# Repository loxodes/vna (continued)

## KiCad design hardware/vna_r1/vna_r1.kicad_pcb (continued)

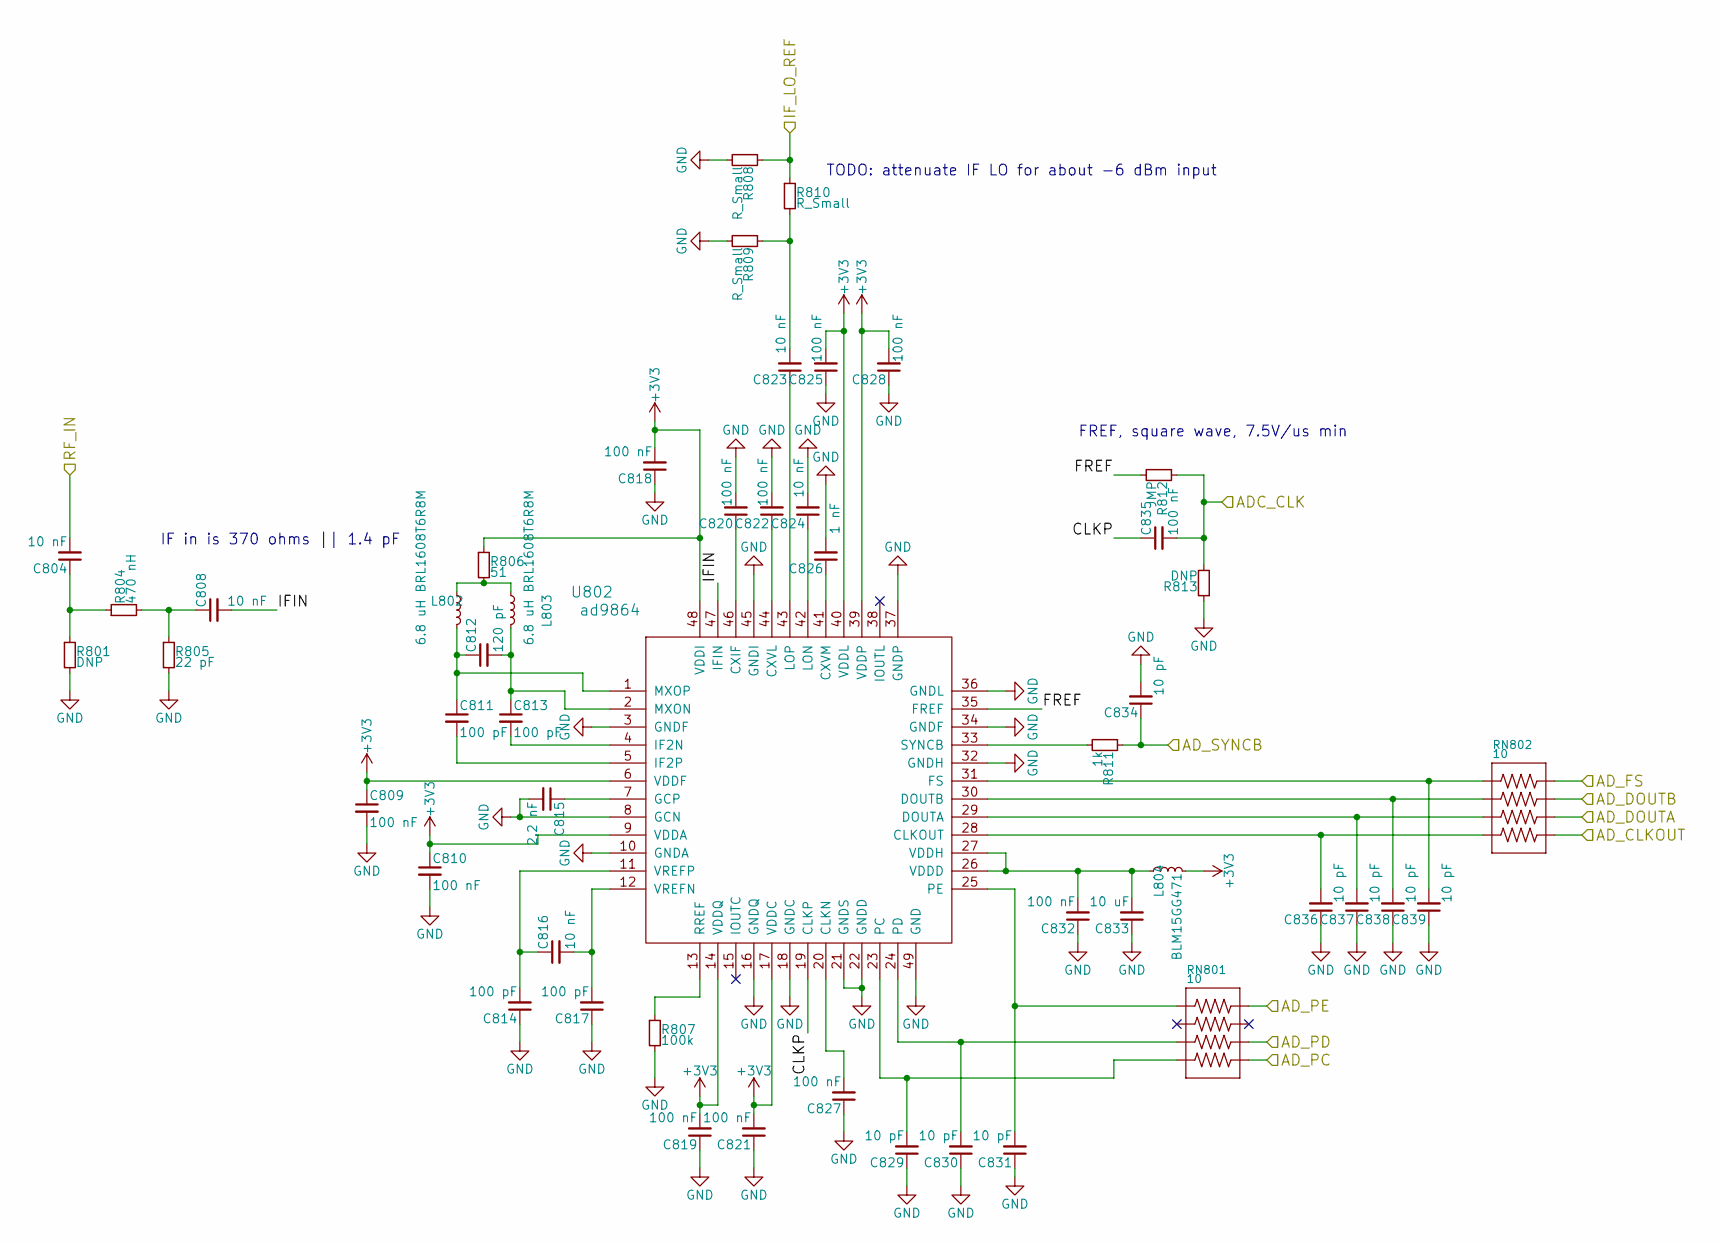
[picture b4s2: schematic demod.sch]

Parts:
C504, C508, C516, C523, C524: 10 nF; C_0402
C509, C510, C518, C519, C520, C521, C522, C525, C527, C528, C532, C535: 100 nF; C_0402
C511, C513, C514, C517: 100 pF; C_0402
C512: 120 pF; C_0402
C515: 2.2 nF; C_0402
C526: 1 nF; C_0402
C529, C530, C531, C534, C536, C537, C538, C539: 10 pF; C_0402
C533: 10 uF; C_0603
L502, L503: 6.8 uH BRL1608T6R8M; R_0603
L504: BLM15GG471; R_0402
R501, R513: DNP; R_0402
R504: 470 nH; R_0402
R505: 22 pF; R_0402
R506: 51; R_0402
R507: 100k; R_0402
R508, R509, R510: R_Small; R_0402
R511: 1k; R_0402
R512: JMP; R_0402
RN501, RN502: 10; RN0804
U502: ad9864; QFN-48-1EP_7x7mm_Pitch0.5mm

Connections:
+3V3: C509.1, C510.1, C518.2, C519.2, C521.2, C525.2, C528.2, L504.2, R506.1, U502.6 (VDDF), U502.9 (VDDA), U502.14 (VDDQ), U502.17 (VDDC), U502.39 (VDDP), U502.40 (VDDL), U502.48 (VDDI); also elsewhere on the board
/ADC_CLK_A: C535.2, R512.1, R513.2; also elsewhere on the board
/AD_CLKOUT: RN502.5; also elsewhere on the board
/AD_DOUTA_A: RN502.6; also elsewhere on the board
/AD_DOUTB: RN502.7; also elsewhere on the board
/AD_FS: RN502.8; also elsewhere on the board
/AD_PC: RN501.5; also elsewhere on the board
/AD_PD: RN501.6; also elsewhere on the board
/AD_PE_A: RN501.8; also elsewhere on the board
/AD_SYNCB: C534.1, R511.1; also elsewhere on the board
/IF_REF_A: R508.1, R510.1; also elsewhere on the board
/demod_a/CLKP: C535.1, U502.19 (CLKP)
/demod_a/FREF: R512.2, U502.35 (FREF)
/demod_a/IFIN: C508.2, U502.47 (IFIN)
/front_panel/DEMOD_1: C504.2; also elsewhere on the board
GND: C509.2, C510.2, C514.1, C515.2, C517.1, C518.1, C519.1, C520.2, C521.1, C522.2, C524.2, C525.1, C526.2, C527.1, C528.1, C529.1, C530.1, C531.1, C532.1, C533.1, C534.2, C536.1, C537.1, C538.1, C539.1, R501.2, R505.2, R507.2, R508.2, R509.2, R513.1, U502.3 (GNDF), U502.8 (GCN), U502.10 (GNDA), U502.16 (GNDQ), U502.18 (GNDC), U502.21 (GNDS), U502.22 (GNDD), U502.32 (GNDH), U502.34 (GNDF), U502.36 (GNDL), U502.37 (GNDP), U502.45 (GNDI), U502.49 (GND); also elsewhere on the board
unnamed: C504.1, R501.1, R504.1
unnamed: C508.1, R504.2, R505.1
unnamed: C511.1, C512.1, L502.2, U502.1 (MXOP)
unnamed: C511.2, U502.5 (IF2P)
unnamed: C512.2, C513.1, L503.2, U502.2 (MXON)
unnamed: C513.2, U502.4 (IF2N)
unnamed: C514.2, C516.1, U502.11 (VREFP)
unnamed: C515.1, U502.7 (GCP)
unnamed: C516.2, C517.2, U502.12 (VREFN)
unnamed: C520.1, U502.46 (CXIF)
unnamed: C522.1, U502.44 (CXVL)
unnamed: C523.1, U502.43 (LOP)
unnamed: C523.2, R509.1, R510.2
unnamed: C524.1, U502.42 (LON)
unnamed: C526.1, U502.41 (CXVM)
unnamed: C527.2, U502.20 (CLKN)
unnamed: C529.2, RN501.4, U502.23 (PC)
unnamed: C530.2, RN501.3, U502.24 (PD)
unnamed: C531.2, RN501.1, U502.25 (PE)
unnamed: C532.2, C533.2, L504.1, U502.26 (VDDD), U502.27 (VDDH)
unnamed: C536.2, RN502.4, U502.28 (CLKOUT)
unnamed: C537.2, RN502.3, U502.29 (DOUTA)
unnamed: C538.2, RN502.2, U502.30 (DOUTB)
unnamed: C539.2, RN502.1, U502.31 (FS)
unnamed: L502.1, L503.1, R506.2
unnamed: R507.1, U502.13 (RREF)
unnamed: R511.2, U502.33 (SYNCB)

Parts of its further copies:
C604, C608, C616, C623, C624, C704, C708, C716, C723, C724, C804, C808, C816, C823, C824: 10 nF; C_0402
C609, C610, C618, C619, C620, C621, C622, C625, C627, C628, C632, C635, C709, C710, C718, C719, C720, C721, C722, C725, C727, C728, C732, C735, C809, C810, C818, C819, C820, C821, C822, C825, C827, C828, C832, C835: 100 nF; C_0402
C611, C613, C614, C617, C711, C713, C714, C717, C811, C813, C814, C817: 100 pF; C_0402
C612, C712, C812: 120 pF; C_0402
C615, C715, C815: 2.2 nF; C_0402
C626, C726, C826: 1 nF; C_0402
C629, C630, C631, C634, C636, C637, C638, C639, C729, C730, C731, C734, C736, C737, C738, C739, C829, C830, C831, C834, C836, C837, C838, C839: 10 pF; C_0402
C633, C733, C833: 10 uF; C_0603
L602, L603, L702, L703, L802, L803: 6.8 uH BRL1608T6R8M; R_0603
L604, L704, L804: BLM15GG471; R_0402
R601, R613, R701, R713, R801, R813: DNP; R_0402
R604, R704, R804: 470 nH; R_0402
R605, R705, R805: 22 pF; R_0402
R606, R706, R806: 51; R_0402
R607, R707, R807: 100k; R_0402
R608, R609, R610, R708, R709, R710, R808, R809, R810: R_Small; R_0402
R611, R711, R811: 1k; R_0402
R612, R712, R812: JMP; R_0402
RN601, RN602, RN701, RN702, RN801, RN802: 10; RN0804
U602, U702, U802: ad9864; QFN-48-1EP_7x7mm_Pitch0.5mm

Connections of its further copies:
+3V3: C609.1, C610.1, C618.2, C619.2, C621.2, C625.2, C628.2, C709.1, C710.1, C718.2, C719.2, C721.2, C725.2, C728.2, C809.1, C810.1, C818.2, C819.2, C821.2, C825.2, C828.2, L604.2, L704.2, L804.2, R606.1, R706.1, R806.1, U602.6 (VDDF), U602.9 (VDDA), U602.14 (VDDQ), U602.17 (VDDC), U602.39 (VDDP), U602.40 (VDDL), U602.48 (VDDI), U702.6 (VDDF), U702.9 (VDDA), U702.14 (VDDQ), U702.17 (VDDC), U702.39 (VDDP), U702.40 (VDDL), U702.48 (VDDI), U802.6 (VDDF), U802.9 (VDDA), U802.14 (VDDQ), U802.17 (VDDC), U802.39 (VDDP), U802.40 (VDDL), U802.48 (VDDI); also elsewhere on the board
/ADC_CLK_B: C635.2, R612.1, R613.2; also elsewhere on the board
/ADC_CLK_C: C735.2, R712.1, R713.2; also elsewhere on the board
/ADC_CLK_D: C835.2, R812.1, R813.2; also elsewhere on the board
/AD_DOUTA_B: RN602.6; also elsewhere on the board
/AD_DOUTA_C: RN702.6; also elsewhere on the board
/AD_DOUTA_D: RN802.6; also elsewhere on the board
/AD_DOUTB: RN602.7, RN702.7, RN802.7; also elsewhere on the board
/AD_PC: RN601.5, RN701.5, RN801.5; also elsewhere on the board
/AD_PD: RN601.6, RN701.6, RN801.6; also elsewhere on the board
/AD_PE_B: RN601.8; also elsewhere on the board
/AD_PE_C: RN701.8; also elsewhere on the board
/AD_PE_D: RN801.8; also elsewhere on the board
/AD_SYNCB: C634.1, C734.1, C834.1, R611.1, R711.1, R811.1; also elsewhere on the board
/IF_REF_B: R608.1, R610.1; also elsewhere on the board
/IF_REF_C: R708.1, R710.1; also elsewhere on the board
/IF_REF_D: R808.1, R810.1; also elsewhere on the board
/demod_b/CLKP: C635.1, U602.19 (CLKP)
/demod_b/FREF: R612.2, U602.35 (FREF)
/demod_b/IFIN: C608.2, U602.47 (IFIN)
/demod_c/CLKP: C735.1, U702.19 (CLKP)
/demod_c/FREF: R712.2, U702.35 (FREF)
/demod_c/IFIN: C708.2, U702.47 (IFIN)
/demod_d/CLKP: C835.1, U802.19 (CLKP)
/demod_d/FREF: R812.2, U802.35 (FREF)
/demod_d/IFIN: C808.2, U802.47 (IFIN)
/front_panel/DEMOD_2: C604.2; also elsewhere on the board
/front_panel/DEMOD_3: C704.2; also elsewhere on the board
/front_panel/DEMOD_4: C804.2; also elsewhere on the board
GND: C609.2, C610.2, C614.1, C615.2, C617.1, C618.1, C619.1, C620.2, C621.1, C622.2, C624.2, C625.1, C626.2, C627.1, C628.1, C629.1, C630.1, C631.1, C632.1, C633.1, C634.2, C636.1, C637.1, C638.1, C639.1, C709.2, C710.2, C714.1, C715.2, C717.1, C718.1, C719.1, C720.2, C721.1, C722.2, C724.2, C725.1, C726.2, C727.1, C728.1, C729.1, C730.1, C731.1, C732.1, C733.1, C734.2, C736.1, C737.1, C738.1, C739.1, C809.2, C810.2, C814.1, C815.2, C817.1, C818.1, C819.1, C820.2, C821.1, C822.2, C824.2, C825.1, C826.2, C827.1, C828.1, C829.1, C830.1, C831.1, C832.1, C833.1, C834.2, C836.1, C837.1, C838.1, C839.1, R601.2, R605.2, R607.2, R608.2, R609.2, R613.1, R701.2, R705.2, R707.2, R708.2, R709.2, R713.1, R801.2, R805.2, R807.2, R808.2, R809.2, R813.1, U602.3 (GNDF), U602.8 (GCN), U602.10 (GNDA), U602.16 (GNDQ), U602.18 (GNDC), U602.21 (GNDS), U602.22 (GNDD), U602.32 (GNDH), U602.34 (GNDF), U602.36 (GNDL), U602.37 (GNDP), U602.45 (GNDI), U602.49 (GND), U702.3 (GNDF), U702.8 (GCN), U702.10 (GNDA), U702.16 (GNDQ), U702.18 (GNDC), U702.21 (GNDS), U702.22 (GNDD), U702.32 (GNDH), U702.34 (GNDF), U702.36 (GNDL), U702.37 (GNDP), U702.45 (GNDI), U702.49 (GND), U802.3 (GNDF), U802.8 (GCN), U802.10 (GNDA), U802.16 (GNDQ), U802.18 (GNDC), U802.21 (GNDS), U802.22 (GNDD), U802.32 (GNDH), U802.34 (GNDF), U802.36 (GNDL), U802.37 (GNDP), U802.45 (GNDI), U802.49 (GND); also elsewhere on the board
unnamed: C604.1, R601.1, R604.1
unnamed: C608.1, R604.2, R605.1
unnamed: C611.1, C612.1, L602.2, U602.1 (MXOP)
unnamed: C611.2, U602.5 (IF2P)
unnamed: C612.2, C613.1, L603.2, U602.2 (MXON)
unnamed: C613.2, U602.4 (IF2N)
unnamed: C614.2, C616.1, U602.11 (VREFP)
unnamed: C615.1, U602.7 (GCP)
unnamed: C616.2, C617.2, U602.12 (VREFN)
unnamed: C620.1, U602.46 (CXIF)
unnamed: C622.1, U602.44 (CXVL)
unnamed: C623.1, U602.43 (LOP)
unnamed: C623.2, R609.1, R610.2
unnamed: C624.1, U602.42 (LON)
unnamed: C626.1, U602.41 (CXVM)
unnamed: C627.2, U602.20 (CLKN)
unnamed: C629.2, RN601.4, U602.23 (PC)
unnamed: C630.2, RN601.3, U602.24 (PD)
unnamed: C631.2, RN601.1, U602.25 (PE)
unnamed: C632.2, C633.2, L604.1, U602.26 (VDDD), U602.27 (VDDH)
unnamed: C636.2, RN602.4, U602.28 (CLKOUT)
unnamed: C637.2, RN602.3, U602.29 (DOUTA)
unnamed: C638.2, RN602.2, U602.30 (DOUTB)
unnamed: C639.2, RN602.1, U602.31 (FS)
unnamed: C704.1, R701.1, R704.1
unnamed: C708.1, R704.2, R705.1
unnamed: C711.1, C712.1, L702.2, U702.1 (MXOP)
unnamed: C711.2, U702.5 (IF2P)
unnamed: C712.2, C713.1, L703.2, U702.2 (MXON)
unnamed: C713.2, U702.4 (IF2N)
unnamed: C714.2, C716.1, U702.11 (VREFP)
unnamed: C715.1, U702.7 (GCP)
unnamed: C716.2, C717.2, U702.12 (VREFN)
unnamed: C720.1, U702.46 (CXIF)
unnamed: C722.1, U702.44 (CXVL)
unnamed: C723.1, U702.43 (LOP)
unnamed: C723.2, R709.1, R710.2
unnamed: C724.1, U702.42 (LON)
unnamed: C726.1, U702.41 (CXVM)
unnamed: C727.2, U702.20 (CLKN)
unnamed: C729.2, RN701.4, U702.23 (PC)
unnamed: C730.2, RN701.3, U702.24 (PD)
unnamed: C731.2, RN701.1, U702.25 (PE)
unnamed: C732.2, C733.2, L704.1, U702.26 (VDDD), U702.27 (VDDH)
unnamed: C736.2, RN702.4, U702.28 (CLKOUT)
unnamed: C737.2, RN702.3, U702.29 (DOUTA)
unnamed: C738.2, RN702.2, U702.30 (DOUTB)
unnamed: C739.2, RN702.1, U702.31 (FS)
unnamed: C804.1, R801.1, R804.1
unnamed: C808.1, R804.2, R805.1
unnamed: C811.1, C812.1, L802.2, U802.1 (MXOP)
unnamed: C811.2, U802.5 (IF2P)
unnamed: C812.2, C813.1, L803.2, U802.2 (MXON)
unnamed: C813.2, U802.4 (IF2N)
unnamed: C814.2, C816.1, U802.11 (VREFP)
unnamed: C815.1, U802.7 (GCP)
unnamed: C816.2, C817.2, U802.12 (VREFN)
unnamed: C820.1, U802.46 (CXIF)
unnamed: C822.1, U802.44 (CXVL)
unnamed: C823.1, U802.43 (LOP)
unnamed: C823.2, R809.1, R810.2
unnamed: C824.1, U802.42 (LON)
unnamed: C826.1, U802.41 (CXVM)
unnamed: C827.2, U802.20 (CLKN)
unnamed: C829.2, RN801.4, U802.23 (PC)
unnamed: C830.2, RN801.3, U802.24 (PD)
unnamed: C831.2, RN801.1, U802.25 (PE)
unnamed: C832.2, C833.2, L804.1, U802.26 (VDDD), U802.27 (VDDH)
unnamed: C836.2, RN802.4, U802.28 (CLKOUT)
unnamed: C837.2, RN802.3, U802.29 (DOUTA)
unnamed: C838.2, RN802.2, U802.30 (DOUTB)
unnamed: C839.2, RN802.1, U802.31 (FS)
unnamed: L602.1, L603.1, R606.2
unnamed: L702.1, L703.1, R706.2
unnamed: L802.1, L803.1, R806.2
unnamed: R607.1, U602.13 (RREF)
unnamed: R611.2, U602.33 (SYNCB)
unnamed: R707.1, U702.13 (RREF)
unnamed: R711.2, U702.33 (SYNCB)
unnamed: R807.1, U802.13 (RREF)
unnamed: R811.2, U802.33 (SYNCB)

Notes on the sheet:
FREF, square wave, 7.5V/us min
IF in is 370 ohms || 1.4 pF
TODO: attenuate IF LO for about -6 dBm input

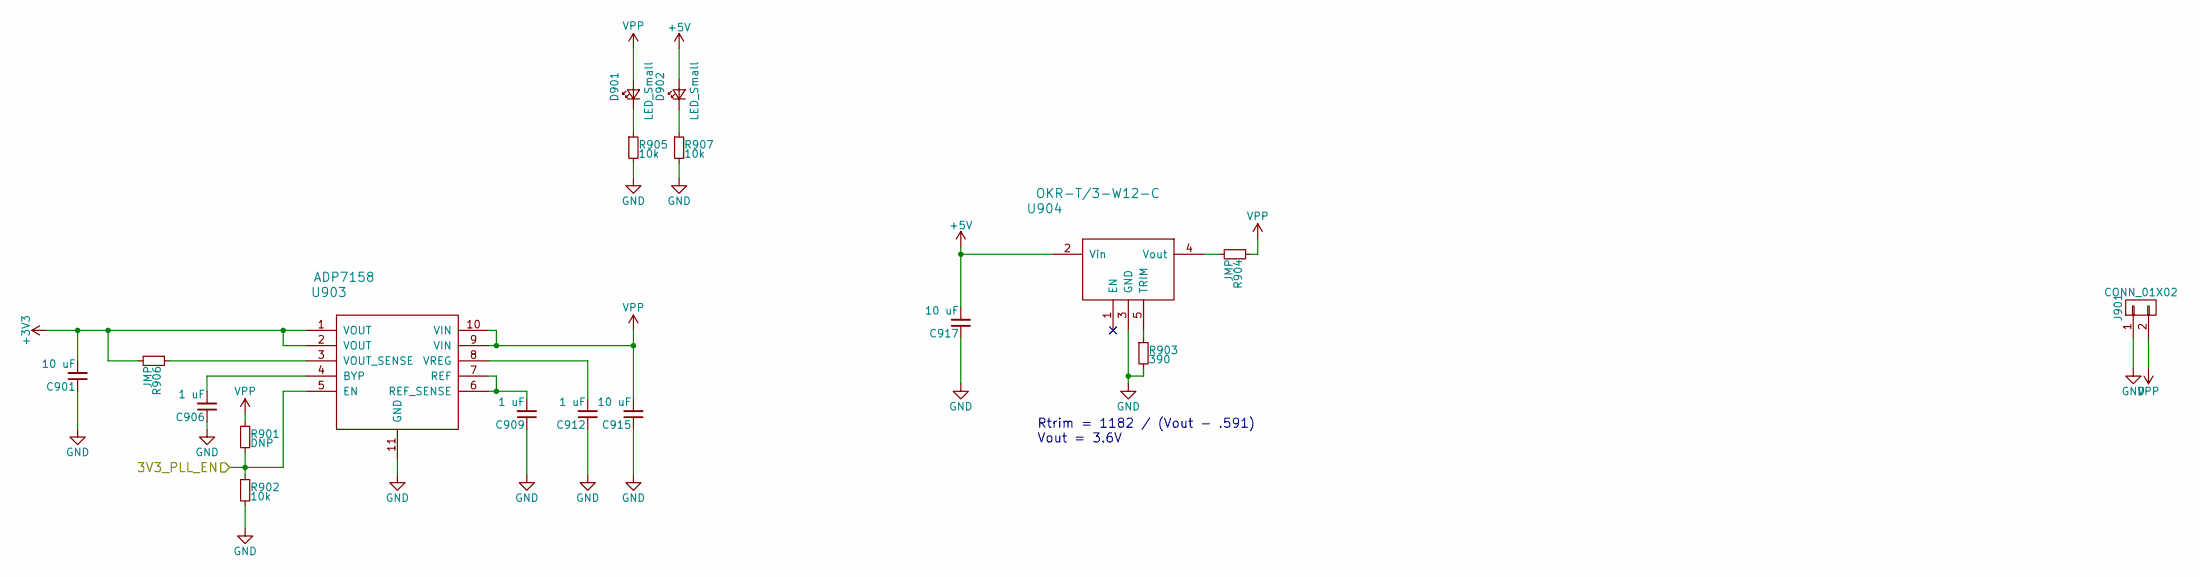
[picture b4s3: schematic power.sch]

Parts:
C901, C915, C917: 10 uF; C_0603
C906, C909, C912: 1 uF; C_0402
D901, D902: LED_Small; LED_0603
J901: CONN_01X02; TerminalBlock_Pheonix_PT-3.5mm_2pol
R901: DNP; R_0402
R902, R905, R907: 10k; R_0402
R903: 390; R_0402
R904: JMP; R_1206
R906: JMP; R_0402
U903: ADP7158; DFN-10-1EP_3x3mm_Pitch0.5mm
U904: OKR-T/3-W12-C; OKRT3_C72

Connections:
+3V3: C901.2, R906.2, U903.1 (VOUT), U903.2 (VOUT); also elsewhere on the board
+5V: C917.2, D902.2 (A), U904.2 (Vin); also elsewhere on the board
/3V3_PLL_EN: R901.2, R902.1, U903.5 (EN); also elsewhere on the board
GND: C901.1, C906.1, C909.1, C912.1, C915.1, C917.1, J901.1, R902.2, R903.2, R905.2, R907.2, U903.11 (GND), U904.3 (GND); also elsewhere on the board
unnamed: C906.2, U903.4 (BYP)
unnamed: C909.2, U903.6 (REF_SENSE), U903.7 (REF)
unnamed: C912.2, U903.8 (VREG)
unnamed: D901.1 (K), R905.1
unnamed: D902.1 (K), R907.1
unnamed: R903.1, U904.5 (TRIM)
unnamed: R904.2, U904.4 (Vout)
unnamed: R906.1, U903.3 (VOUT_SENSE)
VPP: C915.2, D901.2 (A), J901.2, R901.1, R904.1, U903.9 (VIN), U903.10 (VIN); also elsewhere on the board

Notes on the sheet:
Rtrim = 1182 / (Vout - .591) Vout = 3.6V

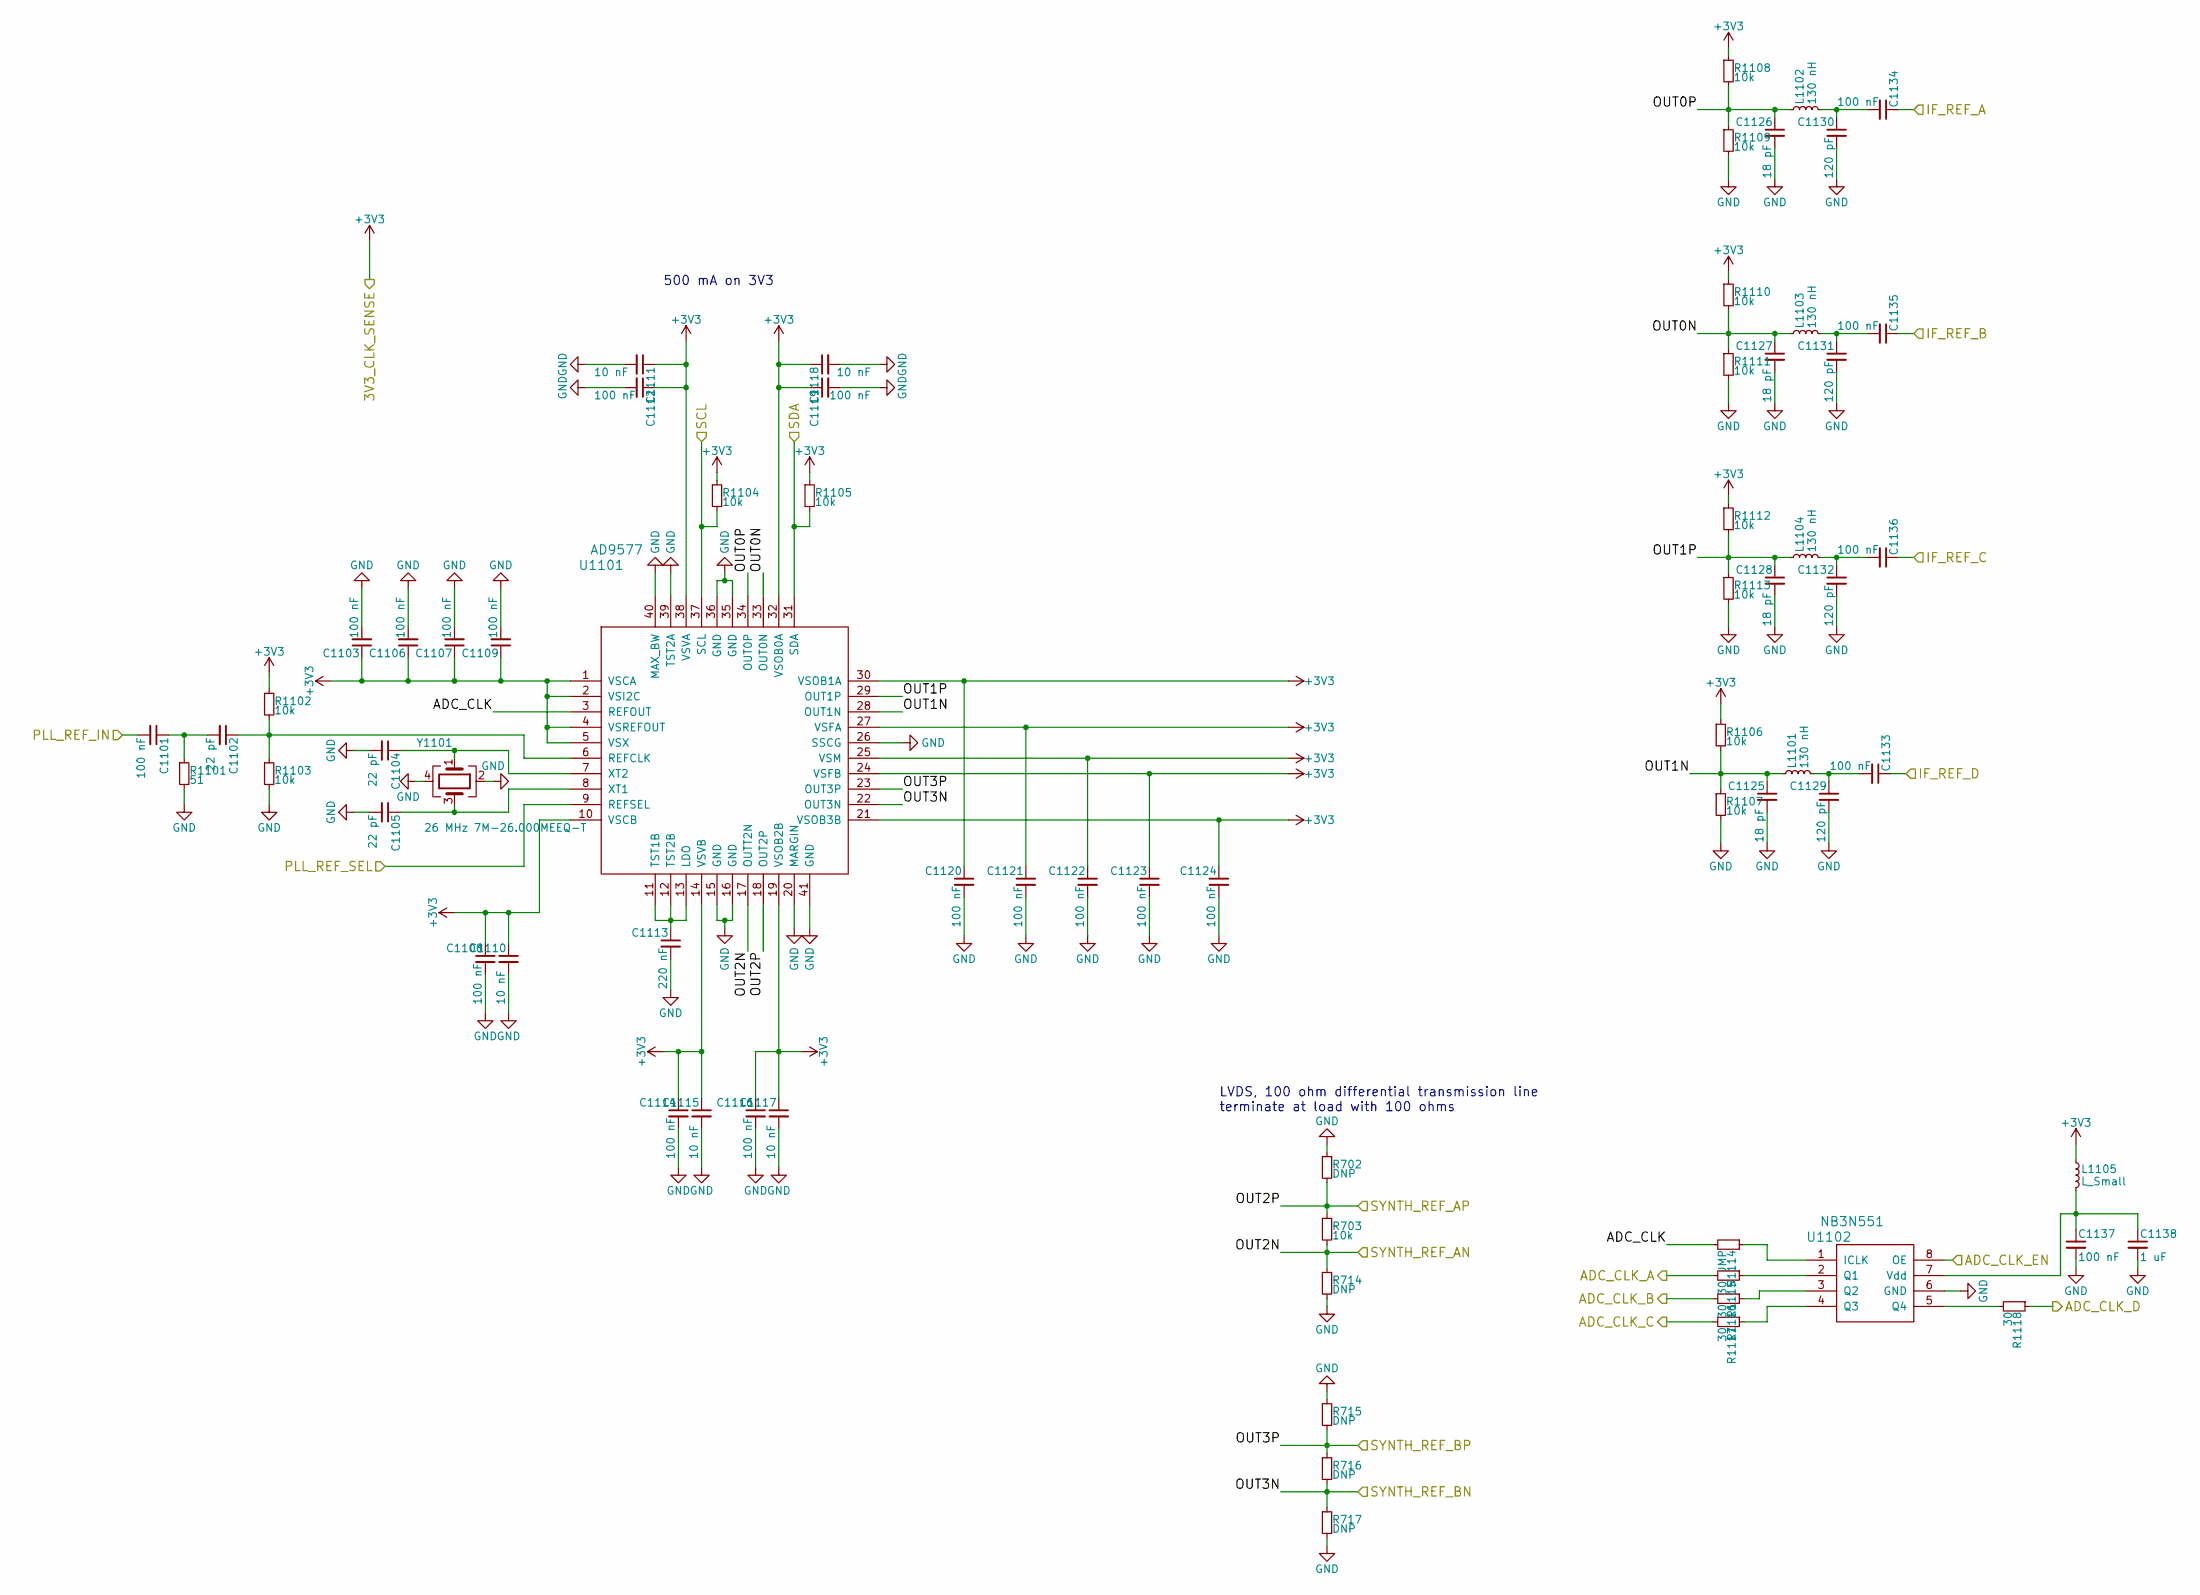
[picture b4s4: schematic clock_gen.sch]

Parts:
C1101, C1103, C1106, C1107, C1108, C1109, C1112, C1114, C1116, C1119, C1120, C1121, C1122, C1123, C1124, C1133, C1134, C1135, C1136, C1137: 100 nF; C_0402
C1102, C1104, C1105: 22 pF; C_0402
C1110, C1111, C1115, C1117, C1118: 10 nF; C_0402
C1113: 220 nF; C_0402
C1125, C1126, C1127, C1128: 18 pF; C_0402
C1129, C1130, C1131, C1132: 120 pF; C_0402
C1138: 1 uF; C_0402
L1101, L1102, L1103, L1104: 130 nH; R_0805
L1105: L_Small; R_0402
R702, R714, R715, R716, R717: DNP; R_0402
R703, R1102, R1103, R1104, R1105, R1106, R1107, R1108, R1109, R1110, R1111, R1112, R1113: 10k; R_0402
R1101: 51; R_0402
R1114: JMP; R_0402
R1115, R1116, R1117, R1118: 30; R_0402
U1101: AD9577; QFN-40-1EP_6x6mm_Pitch0.5mm
U1102: NB3N551; SOIC-8_3.9x4.9mm_Pitch1.27mm
Y1101: 26 MHz 7M-26.000MEEQ-T; crystal_FA238-TSX3225

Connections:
+3V3: C1103.1, C1106.1, C1107.1, C1108.1, C1109.1, C1110.1, C1111.1, C1112.1, C1114.1, C1115.1, C1116.1, C1117.1, C1118.1, C1119.1, C1120.1, C1121.1, C1122.1, C1123.1, C1124.1, L1105.1, R1102.1, R1104.1, R1105.1, R1106.1, R1108.1, R1110.1, R1112.1, U1101.1 (VSCA), U1101.2 (VSI2C), U1101.4 (VSREFOUT), U1101.5 (VSX), U1101.10 (VSCB), U1101.14 (VSVB), U1101.19 (VSOB2B), U1101.21 (VSOB3B), U1101.24 (VSFB), U1101.25 (VSM), U1101.27 (VSFA), U1101.30 (VSOB1A), U1101.32 (VSOB0A), U1101.38 (VSVA); also elsewhere on the board
/ADC_CLK_A: R1115.2; also elsewhere on the board
/ADC_CLK_B: R1116.2; also elsewhere on the board
/ADC_CLK_C: R1117.2; also elsewhere on the board
/ADC_CLK_D: R1118.1; also elsewhere on the board
/ADC_CLK_EN: U1102.8 (OE); also elsewhere on the board
/EXT_PLL_REF: C1101.2; also elsewhere on the board
/IF_REF_A: C1134.1; also elsewhere on the board
/IF_REF_B: C1135.1; also elsewhere on the board
/IF_REF_C: C1136.1; also elsewhere on the board
/IF_REF_D: C1133.1; also elsewhere on the board
/PLL_REF_SEL: U1101.9 (REFSEL); also elsewhere on the board
/SCL: R1104.2, U1101.37 (SCL); also elsewhere on the board
/SDA: R1105.2, U1101.31 (SDA); also elsewhere on the board
/SYNTH_REF_AN: R703.2, R714.1, U1101.17 (OUTT2N); also elsewhere on the board
/SYNTH_REF_AP: R702.2, R703.1, U1101.18 (OUT2P); also elsewhere on the board
/SYNTH_REF_BN: R716.2, R717.1, U1101.22 (OUT3N); also elsewhere on the board
/SYNTH_REF_BP: R715.2, R716.1, U1101.23 (OUT3P); also elsewhere on the board
/clock_synth/ADC_CLK: R1114.2, U1101.3 (REFOUT)
/clock_synth/OUT0N: C1127.1, L1103.1, R1110.2, R1111.1, U1101.33 (OUT0N)
/clock_synth/OUT0P: C1126.1, L1102.1, R1108.2, R1109.1, U1101.34 (OUT0P)
/clock_synth/OUT1N: C1125.1, L1101.1, R1106.2, R1107.1, U1101.28 (OUT1N)
/clock_synth/OUT1P: C1128.1, L1104.1, R1112.2, R1113.1, U1101.29 (OUT1P)
GND: C1103.2, C1104.2, C1105.2, C1106.2, C1107.2, C1108.2, C1109.2, C1110.2, C1111.2, C1112.2, C1113.2, C1114.2, C1115.2, C1116.2, C1117.2, C1118.2, C1119.2, C1120.2, C1121.2, C1122.2, C1123.2, C1124.2, C1125.2, C1126.2, C1127.2, C1128.2, C1129.2, C1130.2, C1131.2, C1132.2, C1137.2, C1138.2, R702.1, R714.2, R715.1, R717.2, R1101.2, R1103.2, R1107.2, R1109.2, R1111.2, R1113.2, U1101.15 (GND), U1101.16 (GND), U1101.20 (MARGIN), U1101.26 (SSCG), U1101.35 (GND), U1101.36 (GND), U1101.39 (TST2A), U1101.40 (MAX_BW), U1101.41 (GND), U1102.6 (GND), Y1101.2, Y1101.4; also elsewhere on the board
unnamed: C1101.1, C1102.2, R1101.1
unnamed: C1102.1, R1102.2, R1103.1, U1101.6 (REFCLK)
unnamed: C1104.1, U1101.7 (XT2), Y1101.1
unnamed: C1105.1, U1101.8 (XT1), Y1101.3
unnamed: C1113.1, U1101.11 (TST1B), U1101.12 (TST2B), U1101.13 (LDO)
unnamed: C1129.1, C1133.2, L1101.2
unnamed: C1130.1, C1134.2, L1102.2
unnamed: C1131.1, C1135.2, L1103.2
unnamed: C1132.1, C1136.2, L1104.2
unnamed: C1137.1, C1138.1, L1105.2, U1102.7 (Vdd)
unnamed: R1114.1, U1102.1 (ICLK)
unnamed: R1115.1, U1102.2 (Q1)
unnamed: R1116.1, U1102.3 (Q2)
unnamed: R1117.1, U1102.4 (Q3)
unnamed: R1118.2, U1102.5 (Q4)

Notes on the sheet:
500 mA on 3V3
LVDS, 100 ohm differential transmission line terminate at load with 100 ohms

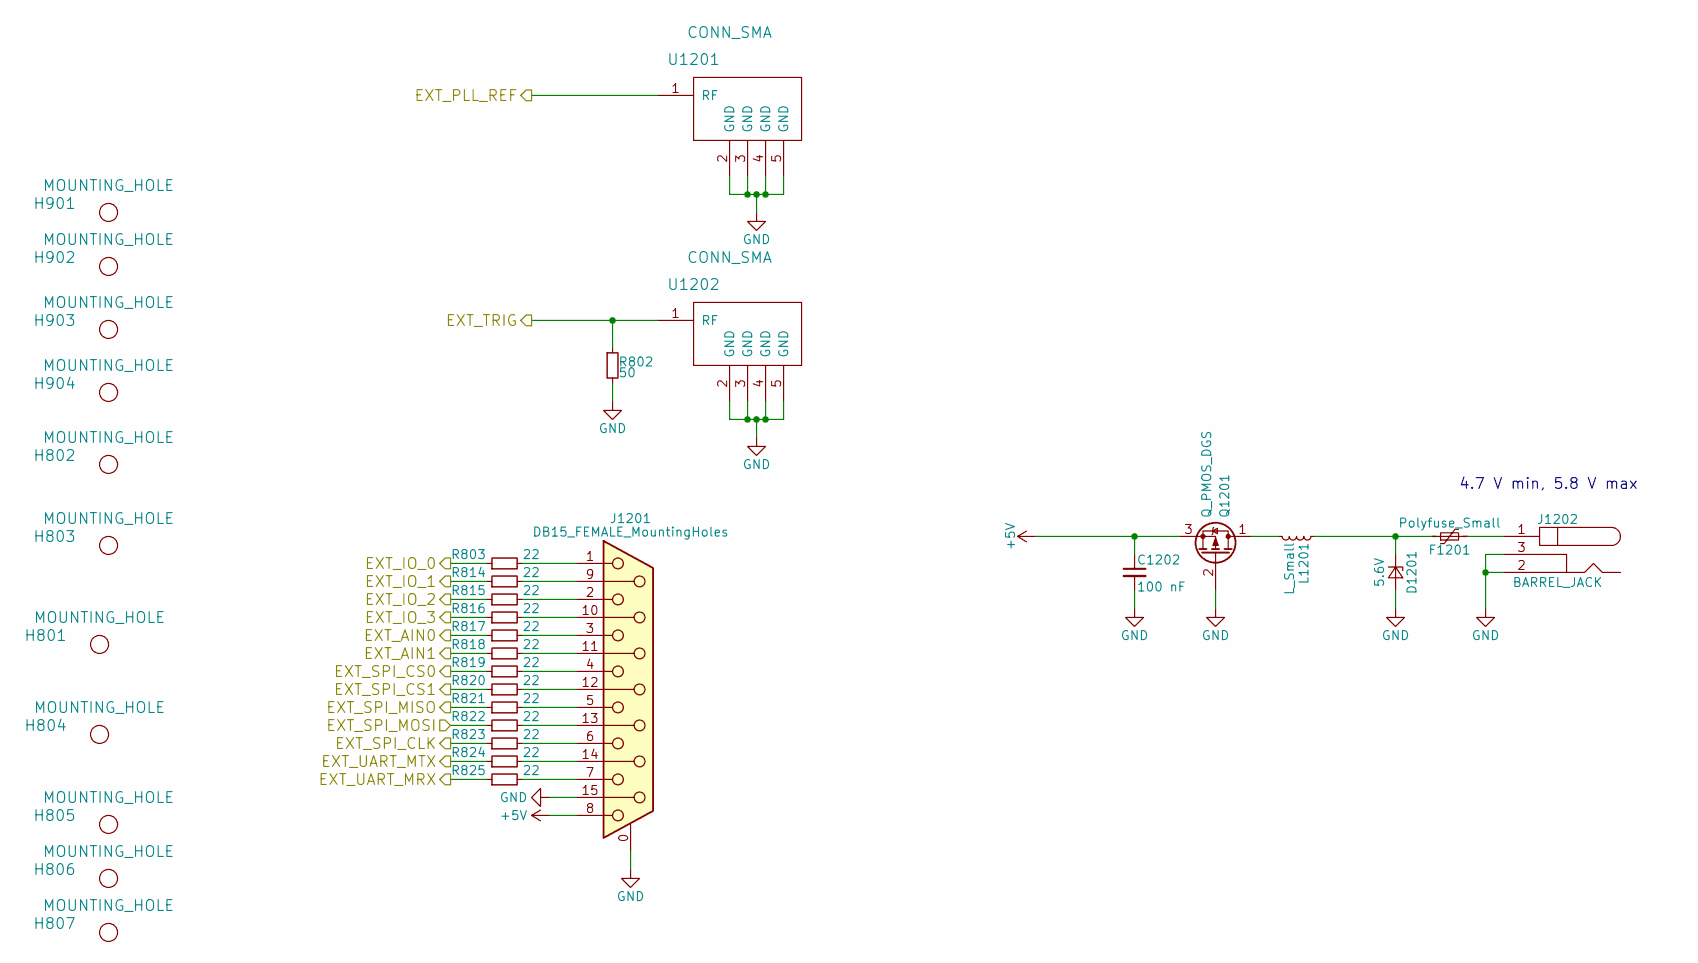
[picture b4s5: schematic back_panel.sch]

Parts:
C1202: 100 nF; C_0402
D1201: 5.6V; SOD-123
F1201: Polyfuse_Small; R_1210
H801, H802, H803, H804, H805, H806, H807, H901, H902, H903, H904: MOUNTING_HOLE; MountingHole_2-5mm
J1201: DB15_FEMALE_MountingHoles; DB15MC
J1202: BARREL_JACK
L1201: L_Small; R_0805
Q1201: Q_PMOS_DGS; SOT-23
R802: 50; R_0402
R803, R814, R815, R816, R817, R818, R819, R820, R821, R822, R823, R824, R825: 22; R_0402
U1201: CONN_SMA; 732511150_sma_thin
U1202: CONN_SMA; 732512200_SMA

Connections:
+5V: C1202.1, J1201.8, Q1201.3 (S); also elsewhere on the board
/EXT_AIN0: R817.1; also elsewhere on the board
/EXT_AIN1: R818.1; also elsewhere on the board
/EXT_IO_0: R803.1; also elsewhere on the board
/EXT_IO_1: R814.1; also elsewhere on the board
/EXT_IO_2: R815.1; also elsewhere on the board
/EXT_IO_3: R816.1; also elsewhere on the board
/EXT_PLL_REF: U1201.1 (RF); also elsewhere on the board
/EXT_SPI_CLK: R823.1; also elsewhere on the board
/EXT_SPI_CS0: R819.1; also elsewhere on the board
/EXT_SPI_CS1: R820.1; also elsewhere on the board
/EXT_SPI_MISO: R821.1; also elsewhere on the board
/EXT_SPI_MOSI: R822.1; also elsewhere on the board
/EXT_TRIG: R802.1, U1202.1 (RF); also elsewhere on the board
/EXT_UART_MRX: R825.1; also elsewhere on the board
/EXT_UART_MTX: R824.1; also elsewhere on the board
GND: C1202.2, D1201.2 (A), J1201.0 (PAD), J1201.15, J1202.2, J1202.3, Q1201.2 (G), R802.2, U1201.2 (GND), U1201.3 (GND), U1201.4 (GND), U1201.5 (GND), U1202.2 (GND), U1202.3 (GND), U1202.4 (GND), U1202.5 (GND); also elsewhere on the board
unnamed: D1201.1 (K), F1201.1, L1201.1
unnamed: F1201.2, J1202.1
unnamed: J1201.1, R803.2
unnamed: J1201.2, R815.2
unnamed: J1201.3, R817.2
unnamed: J1201.4, R819.2
unnamed: J1201.5, R821.2
unnamed: J1201.6, R823.2
unnamed: J1201.7, R825.2
unnamed: J1201.9, R814.2
unnamed: J1201.10, R816.2
unnamed: J1201.11 (P111), R818.2
unnamed: J1201.12, R820.2
unnamed: J1201.13, R822.2
unnamed: J1201.14, R824.2
unnamed: L1201.2, Q1201.1 (D)

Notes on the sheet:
4.7 V min, 5.8 V max
